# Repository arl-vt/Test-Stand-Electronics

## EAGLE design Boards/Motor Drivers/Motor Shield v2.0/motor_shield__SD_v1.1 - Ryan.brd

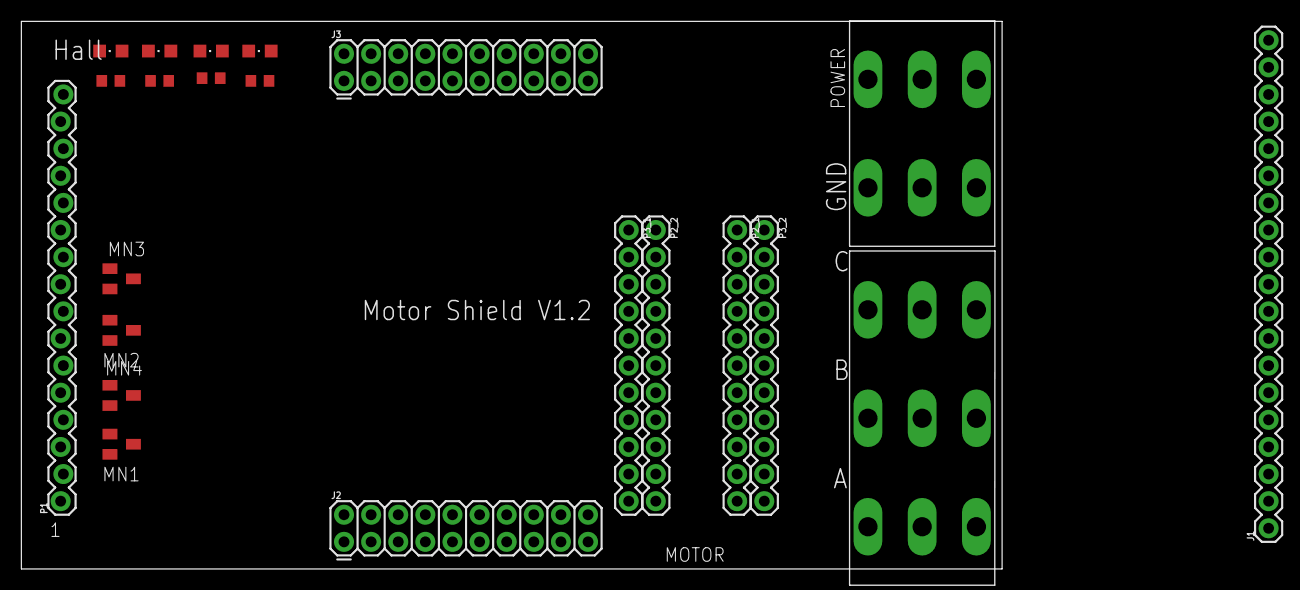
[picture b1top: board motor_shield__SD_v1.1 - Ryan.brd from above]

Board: 2 copper layers, 91.9 x 51.3 mm, 23 parts (1 on the bottom side), 25 nets, no tracks yet.

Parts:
J1: 1X19
J2, J3: 2X10
LED1, LED2, LED3, LED4: CHIPLED_0805
MN1, MN2, MN3, MN4: SOT23
MOTOR: PHOENIX_3POS
P1: 1X16_LOCK
P2_1, P2_2, P3_1, P3_2: 1X11
POWER: PHOENIX_2POS
R1, R2, R3, R4: 220; R0603
X1: PB-53261-05

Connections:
*INHIBIT: MN4.1, P1.5
+5V: R1.2, R2.2, R3.2, R4.2
CURRENT_MONITOR: MN1.1, P1.4
CURRENT_REF: MN2.1, P1.11
DIRECTION: J2.20, P1.3
FAULT_OUT: MN3.1, P1.12
GND: J2.4, J3.2, MN1.2, MN2.2, MN3.2, MN4.2, P1.2, X1.2
HALL1: P1.8, X1.3
HALL2: P1.9, X1.4
HALL3: P1.10, X1.5
HIGH_VOL: P2_1.1, P2_1.2, P2_2.1, P2_2.2, P3_1.1, P3_1.2, P3_2.1, P3_2.2, POWER.4, POWER.5, POWER.6
MOTOR_A: MOTOR.1, MOTOR.2, MOTOR.3, P2_1.10, P2_1.11, P2_2.10, P2_2.11, P3_1.10, P3_1.11, P3_2.10, P3_2.11
MOTOR_B: MOTOR.4, MOTOR.5, MOTOR.6, P2_1.8, P2_1.9, P2_2.8, P2_2.9, P3_1.8, P3_1.9, P3_2.8, P3_2.9
MOTOR_C: MOTOR.7, MOTOR.8, MOTOR.9, P2_1.6, P2_1.7, P2_2.6, P2_2.7, P3_1.6, P3_1.7, P3_2.6, P3_2.7
unnamed: LED1.A, R1.1
unnamed: LED2.A, R2.1
unnamed: LED3.A, R3.1
unnamed: LED4.A, R4.1
unnamed: LED1.C, MN1.3
unnamed: LED2.C, MN2.3
unnamed: LED3.C, MN3.3
unnamed: LED4.C, MN4.3
PWM: J3.12, P1.1
PWR_GND: P2_1.4, P2_1.5, P2_2.4, P2_2.5, P3_1.4, P3_1.5, P3_2.4, P3_2.5, POWER.1, POWER.2, POWER.3
V+_HALL: P1.6, X1.1

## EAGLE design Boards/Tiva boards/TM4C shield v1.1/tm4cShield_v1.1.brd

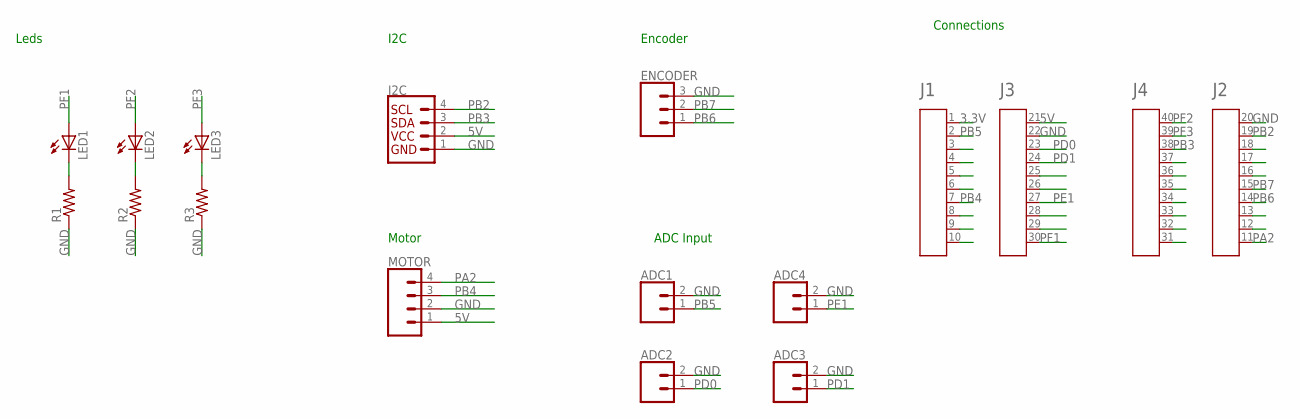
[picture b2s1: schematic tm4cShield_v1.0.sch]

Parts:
A1: HEADER4X10-BOOSTERPACK; 4X10-BOOSTERPACK
ADC1, ADC2, ADC3, ADC4: CONN_02; 1X02
ENCODER: CONN_03JST-PTH-VERT; JST-3-PTH-VERT
I2C: I2C_STANDARD; 1X04
LED1, LED2, LED3: LED0603; LED-0603
MOTOR: CONN_04JST-PTH-VERT; JST-4-PTH-VERT
R1, R2, R3: RESISTOR_0603; RESC0603

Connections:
3.3V: A1.1
5V: A1.21, I2C.2, MOTOR.1
GND: A1.20, A1.22, ADC1.2, ADC2.2, ADC3.2, ADC4.2, ENCODER.3, I2C.1, MOTOR.2, R1.1, R2.1, R3.1
unnamed: LED1.C, R1.2
unnamed: LED2.C, R2.2
unnamed: LED3.C, R3.2
PA2: A1.11, MOTOR.4
PB2: A1.19, I2C.4
PB3: A1.38, I2C.3
PB4: A1.7, MOTOR.3
PB5: A1.2, ADC1.1
PB6: A1.14, ENCODER.1
PB7: A1.15, ENCODER.2
PD0: A1.23, ADC2.1
PD1: A1.24, ADC3.1
PE1: A1.27, ADC4.1
PF1: A1.30, LED1.A
PF2: A1.40, LED2.A
PF3: A1.39, LED3.A

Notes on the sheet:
Leds
Connections
I2C
Encoder
Motor
ADC Input

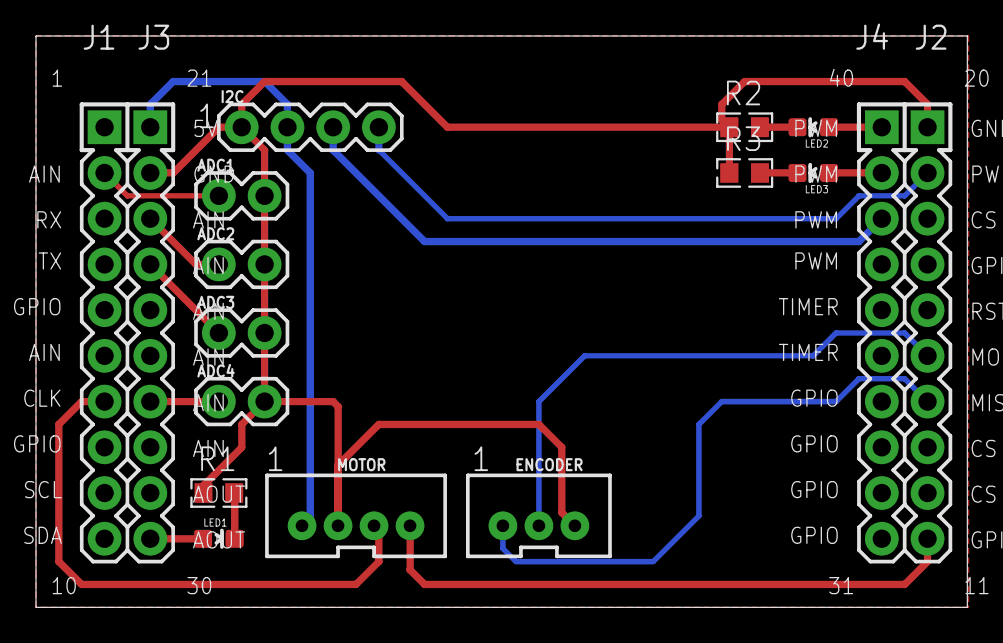
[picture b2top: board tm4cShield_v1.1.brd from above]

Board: 2 copper layers, 51.7 x 31.7 mm, 14 parts (0 on the bottom side), 18 nets.

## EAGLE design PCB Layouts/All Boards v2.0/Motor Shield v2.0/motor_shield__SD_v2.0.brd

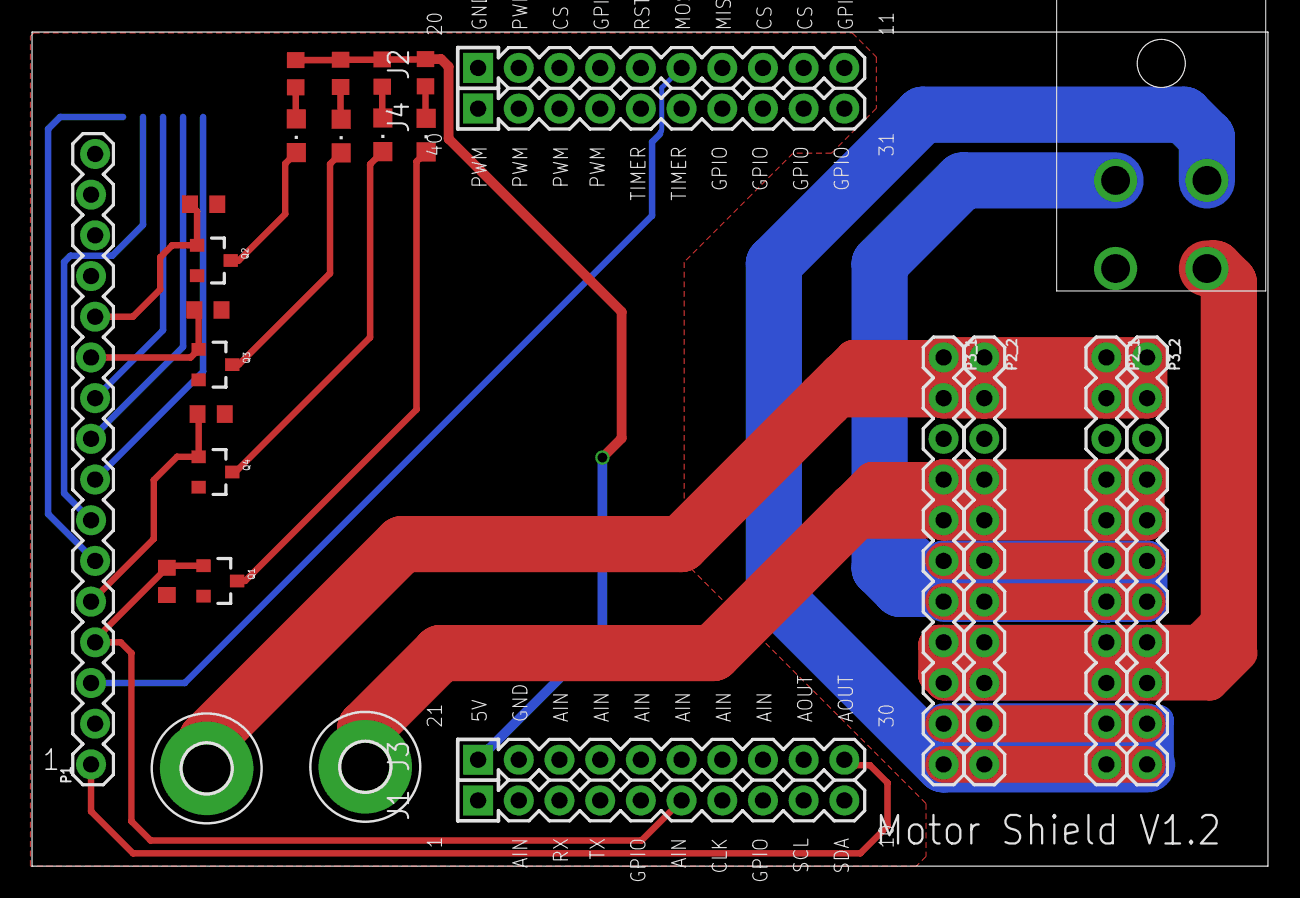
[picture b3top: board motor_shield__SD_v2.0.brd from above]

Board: 2 copper layers, 77.1 x 52.1 mm, 26 parts (1 on the bottom side), 26 nets.

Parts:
A1: 4X10-BOOSTERPACK
C1: MOLEX4CON
H1, H3: MOUNT-PAD-ROUND3.0; 3,0-PAD
LED1, LED2, LED3, LED4: CHIPLED_0805
P1: 1X16_LOCK
P2_1, P2_2, P3_1, P3_2: 1X11
Q1, Q2, Q3, Q4: MMBT2222A; SOT23-3
R1, R2, R3, R4: 220; R0603
R5, R6, R7, R8: 1000; R0603
X1: PB-53261-05

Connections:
*INHIBIT: P1.5, Q4.1, R7.2
+5V: A1.21, R1.2, R2.2, R3.2, R4.2
CURRENT_MONITOR: A1.6, P1.4, Q1.1, R5.2
CURRENT_REF: P1.11, Q3.1, R8.2
DIRECTION: A1.15, P1.3
FAULT_OUT: P1.12, Q2.1, R6.2
GND: A1.22, P1.2, Q1.2, Q2.2, Q3.2, Q4.2, R5.1, R6.1, R7.1, R8.1
GND_HALL: P1.7, X1.2
HALL1: P1.8, X1.5
HALL2: P1.9, X1.4
HALL3: P1.10, X1.3
HIGH_VOL: H3.B3,0, P2_1.1, P2_1.2, P2_2.1, P2_2.2, P3_1.1, P3_1.2, P3_2.1, P3_2.2
MOTOR_A: C1.2, P2_1.10, P2_1.11, P2_2.10, P2_2.11, P3_1.10, P3_1.11, P3_2.10, P3_2.11
MOTOR_B: C1.1, P2_1.8, P2_1.9, P2_2.8, P2_2.9, P3_1.8, P3_1.9, P3_2.8, P3_2.9
MOTOR_C: C1.4, P2_1.6, P2_1.7, P2_2.6, P2_2.7, P3_1.6, P3_1.7, P3_2.6, P3_2.7
unnamed: LED1.A, R1.1
unnamed: LED2.A, R2.1
unnamed: LED3.A, R3.1
unnamed: LED4.A, R4.1
unnamed: LED1.C, Q1.3
unnamed: LED2.C, Q3.3
unnamed: LED3.C, Q2.3
unnamed: LED4.C, Q4.3
PWM: A1.30, P1.1
PWR_GND: H1.B3,0, P2_1.4, P2_1.5, P2_2.4, P2_2.5, P3_1.4, P3_1.5, P3_2.4, P3_2.5
V+_HALL: P1.6, X1.1

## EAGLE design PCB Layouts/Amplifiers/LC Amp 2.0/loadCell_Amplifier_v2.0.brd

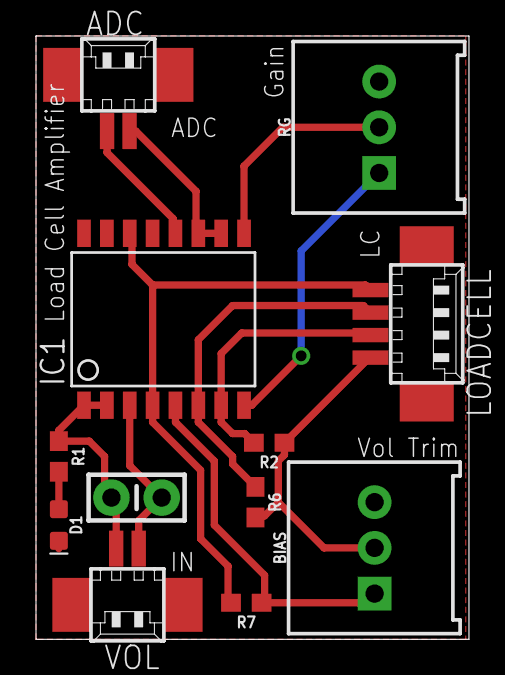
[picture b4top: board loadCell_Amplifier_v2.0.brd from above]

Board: 2 copper layers, 24.1 x 33.5 mm, 12 parts (0 on the bottom side), 10 nets.

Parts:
ADC: 53261-02
BIAS: 10k; TRIMPOT-PTH-3386U
C2: 0.1uF; CAP-PTH-SMALL-KIT
D1: LED-0603
IC1: INA125U; SO16-1
LOADCELL: 53261-04
R1: 330; 0603
R2, R6, R7: 10k; 0603
RG: 10k; TRIMPOT-PTH-3386U
VOL: 53261-02

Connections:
GND: ADC.2, BIAS.2, C2.1, D1.C, IC1.3, IC1.12, LOADCELL.1, R2.1, R6.2, VOL.2
IAREF: BIAS.1, IC1.5, R7.1
unnamed: IC1.8, RG.1
unnamed: IC1.9, RG.2
unnamed: D1.A, R1.2
V+: IC1.6, LOADCELL.3, R6.1
V-: IC1.7, LOADCELL.2, R2.2
VIN: C2.2, IC1.1, IC1.2, R1.1, VOL.1
VO: ADC.1, IC1.10, IC1.11
V_2.5: IC1.4, IC1.14, LOADCELL.4, R7.2

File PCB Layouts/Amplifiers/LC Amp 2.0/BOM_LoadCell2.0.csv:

Part/Designator,DigiKey,Quantity,Description
Con1,WM7620TR-ND,1,"Molex 53261, 2 pos Connector"
Con2,WM7620TR-ND,1,"Molex 53261, 2 pos Connector"
Con3,WM7622TR-ND,1,"Molex 53261, 4 pos Connector"
D1,475-1278-2-ND,1,Red
R1,311-330GRCT-ND,1,"330 ohm, 0603 Resistor"
"R6, R7, R2",311-10.0KHRTR-ND,3,"10 kohm, 0603 resistor"
IC1,INA125U-ND,1,INA125u
C2,BC1160TR-ND,`,0.1 uF Capacitor. Pth
"BIAS, RG",3266Y-1-103LF-ND,2,"10K, trim POT"

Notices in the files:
parts and their libraries:
SparkFun-Connectors: Licensing: Creative Commons ShareAlike 4.0 International - https://creativecommons.org/licenses/by-sa/4.0
